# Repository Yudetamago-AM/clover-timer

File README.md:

# clover-timer
Simple Countdown Timer using Padauk MCU

## Docs
- [組み立て方（Japanese）](./docs/assembly-instruction.pdf)
- [補足資料（Japanese）](./docs/assembly-instruction-short.pdf)

## Schematic

Only supports PMS150G for now, but should be able to run on other Padauk MCUs with modifications.

### Power Consumption
- 350 μA (Countdown)
- 55  μA (Sleep)

Fall sleep in 2.5s

## BOM
| Ref | Part # | Description | Purchase | Price |
| --- | ------ | ----------- | -------- | ----- |
| IC1 | Padauk PMS150G | MCU | [LCSC](https://www.lcsc.com/product-detail/Microcontroller-Units-MCUs-MPUs-SOCs_PADAUK-Tech-PMS150G-S08_C2909819.html) | $0.04 each |
| SW1, SW2| TS4548CJ | Push Switch. Others are OK (Check footprint) | [LCSC](https://www.lcsc.com/product-detail/_SHOU-HAN-_C5359333.html) | $0.008 each |
| BZ1 | SFN-1407PA7.6 | Passive Buzzer | [LCSC](https://www.lcsc.com/product-detail/_S-S-_C360603.html) | $0.05 each |
| Battery | CR2032 | 3V Litium Battery Cell | - | $0.1~ each |
| - | Case | 3D printed case | Print by yourself | [STL](./case/bottom_rev0f.stl) |
| - | Binder Clip | Clip for Battery Case | - | $0.05~  each|
| - | Jigu(Optional) | Cardboard Jigu for Battery Case | Cut by yourself | [Data](./case/jigu_laser_rev2.dxf) |
| - | Magnet(Optional) | Φ18*5mm Magnet | - | $0.05~ each |

## Usage

## License
GPLv3

This project is based on:
- [Padauk-tone](https://github.com/Kashouryo/Padauk-tone) by Kashouryo, MIT License
- [pdk-digital-clock](https://github.com/serisman/pdk-digital-clock) by serisman, GPLv3

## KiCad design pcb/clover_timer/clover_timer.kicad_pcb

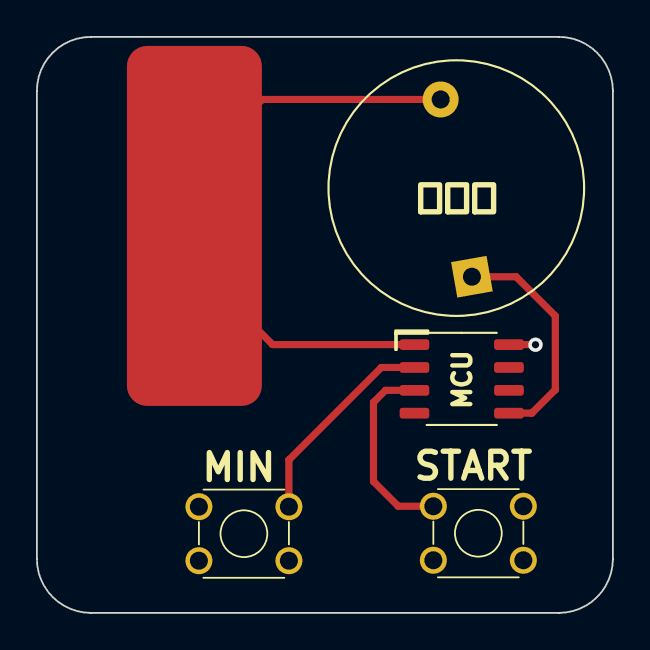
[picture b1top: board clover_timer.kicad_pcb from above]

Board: 2 copper layers, 32.0 x 32.0 mm, 6 parts (1 on the bottom side), 5 nets.

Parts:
BZ1: Buzzer; Buzzer_D14mm_H7mm_P10mm
IC1: PMS150G-S08; SOP-8_3.9x4.9mm_P1.27mm
J1: CR2032_Plus
J2: CR2032_Minus; CR2032_GND
SW1, SW2: SW_Push; SW_TS4548CJ

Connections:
+3V0: BZ1.2 (+), IC1.1 (VDD), J1.1
GND: IC1.8 (GND), J2.1, SW1.1, SW2.1
unnamed: BZ1.1 (-), IC1.5 (PA3)
unnamed: IC1.3 (PA6), SW2.2
unnamed: IC1.2 (PA7), SW1.2

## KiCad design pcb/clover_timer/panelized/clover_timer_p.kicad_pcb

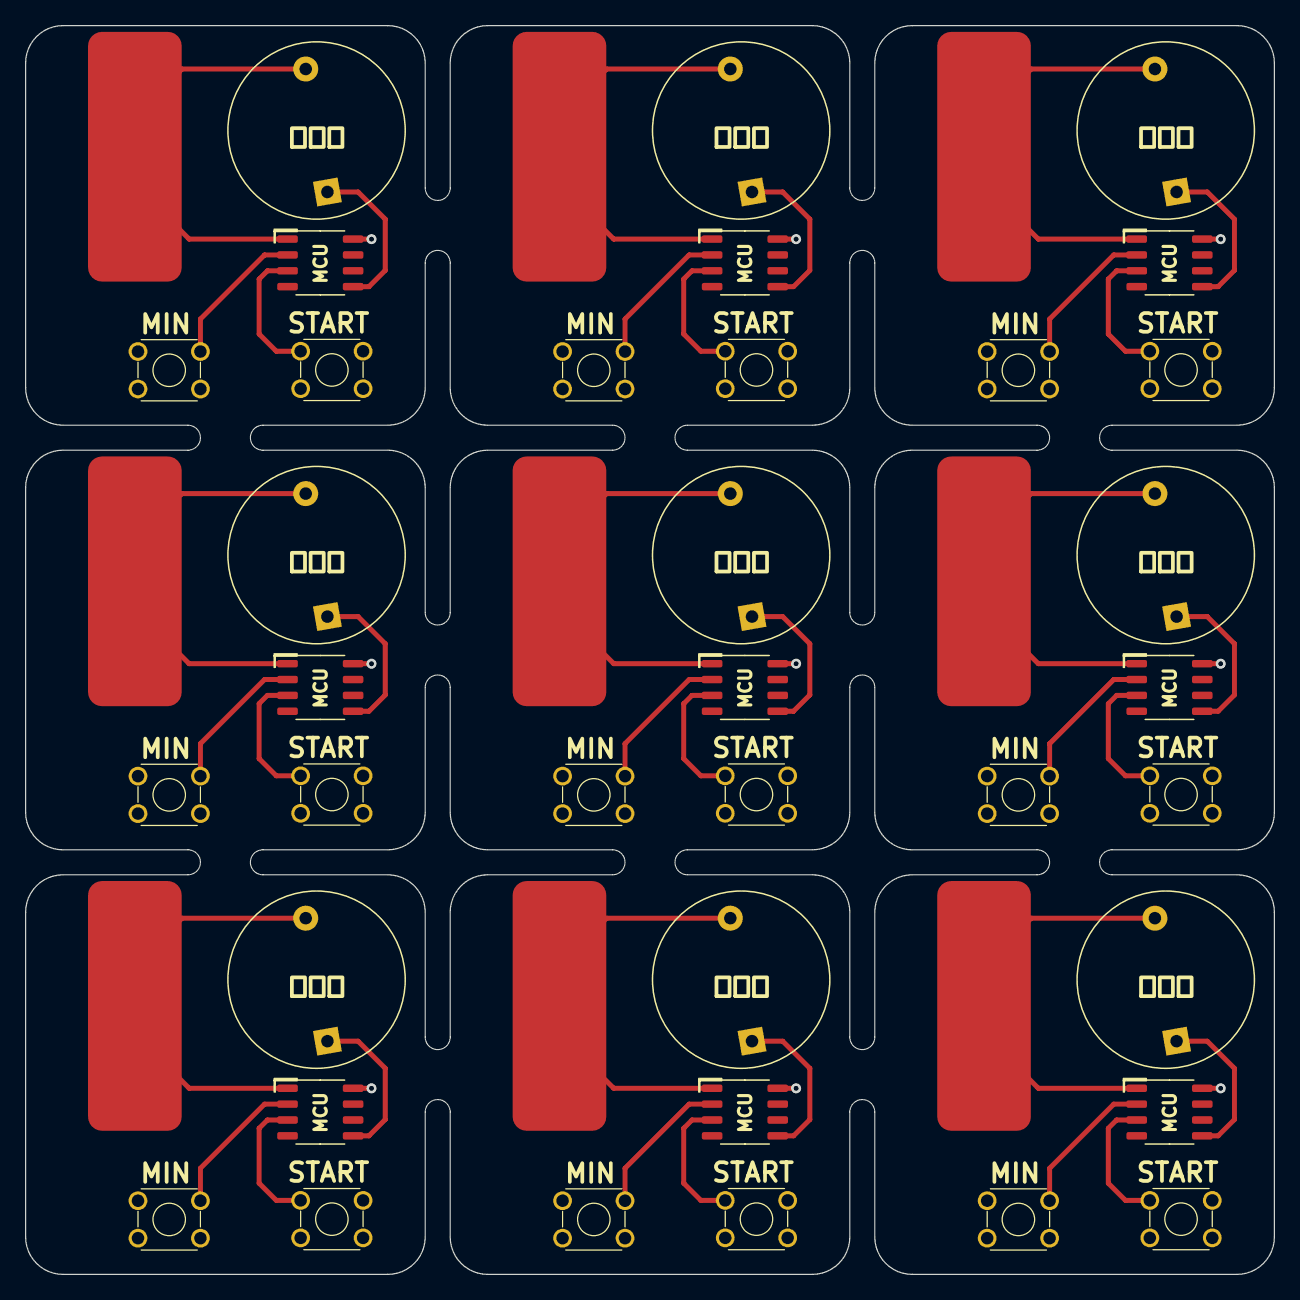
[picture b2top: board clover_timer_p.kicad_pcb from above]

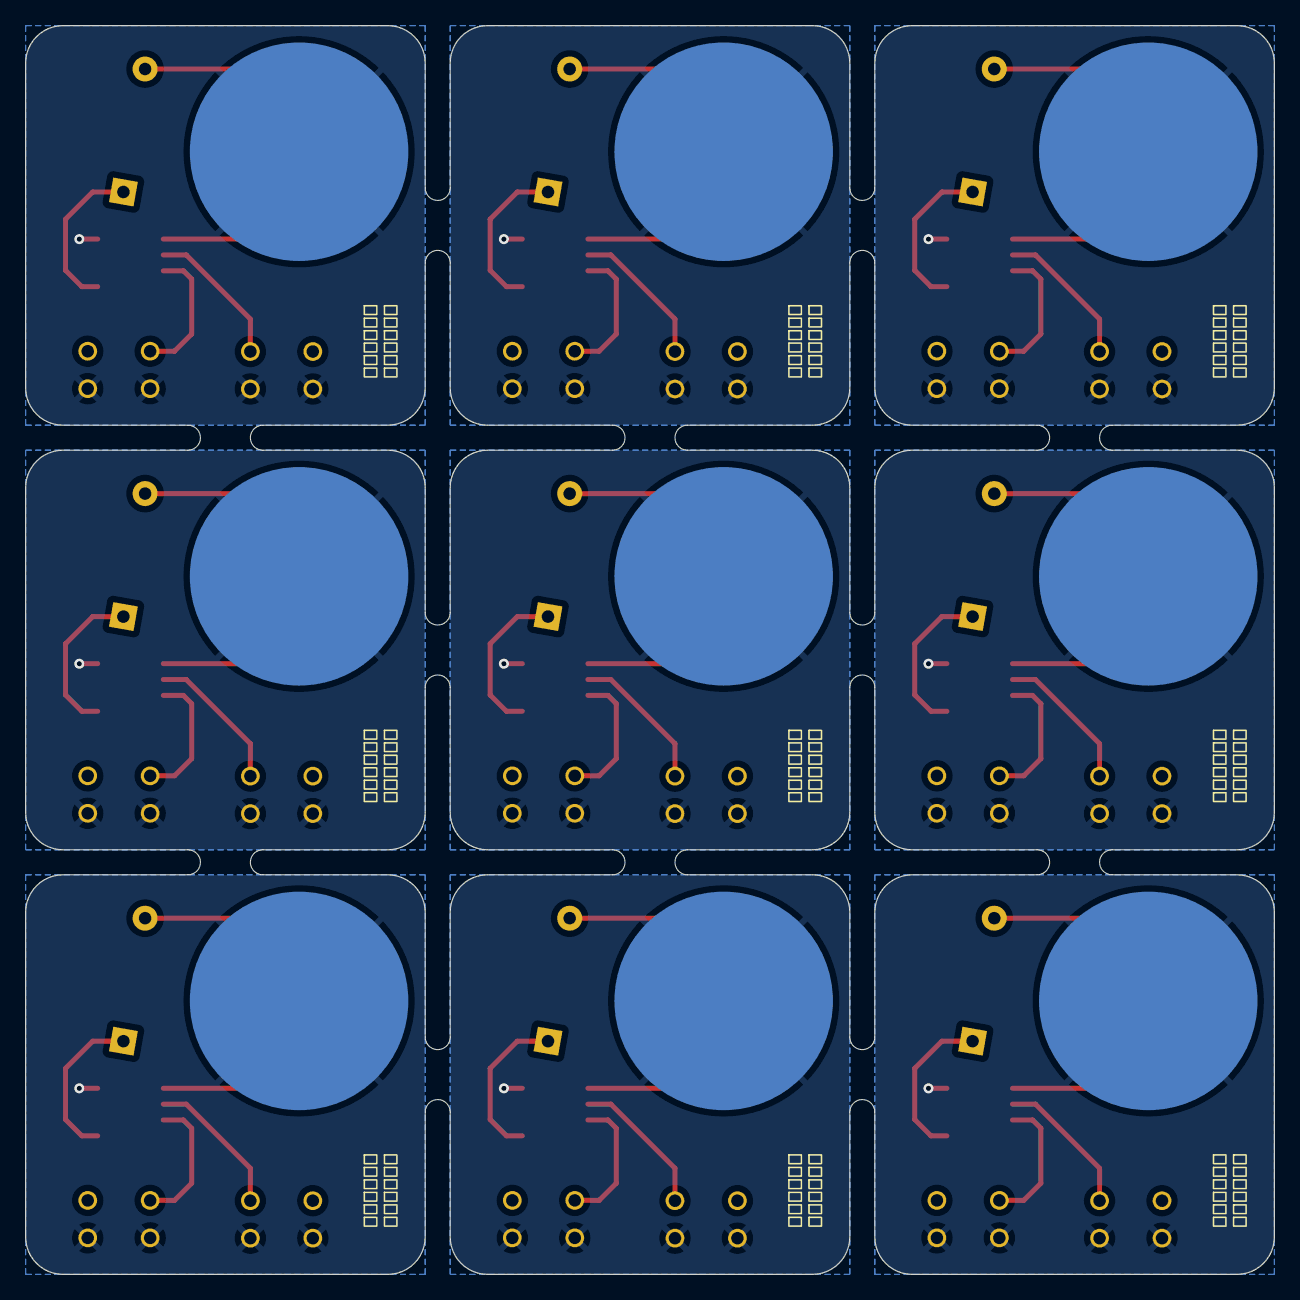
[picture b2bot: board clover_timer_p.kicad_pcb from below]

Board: 2 copper layers, 100.0 x 100.0 mm, 54 parts (9 on the bottom side), 5 nets.

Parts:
BZ1, BZ2, BZ3, BZ4, BZ5, BZ6, BZ7, BZ8, BZ9: Buzzer; Buzzer_D14mm_H7mm_P10mm
IC1, IC2, IC3, IC4, IC5, IC6, IC7, IC8, IC9: PMS150G-S08; SOP-8_3.9x4.9mm_P1.27mm
J1, J3, J5, J7, J9, J11, J13, J15, J17: CR2032_Plus
J2, J4, J6, J8, J10, J12, J14, J16, J18: CR2032_Minus; CR2032_GND
SW1, SW2, SW3, SW4, SW5, SW6, SW7, SW8, SW9, SW10, SW11, SW12, SW13, SW14, SW15, SW16, SW17, SW18: SW_Push; SW_TS4548CJ

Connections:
+3V0: BZ1.2 (+), BZ2.2 (+), BZ3.2 (+), BZ4.2 (+), BZ5.2 (+), BZ6.2 (+), BZ7.2 (+), BZ8.2 (+), BZ9.2 (+), IC1.1 (VDD), IC2.1 (VDD), IC3.1 (VDD), IC4.1 (VDD), IC5.1 (VDD), IC6.1 (VDD), IC7.1 (VDD), IC8.1 (VDD), IC9.1 (VDD), J1.1, J3.1, J5.1, J7.1, J9.1, J11.1, J13.1, J15.1, J17.1
GND: IC1.8 (GND), IC2.8 (GND), IC3.8 (GND), IC4.8 (GND), IC5.8 (GND), IC6.8 (GND), IC7.8 (GND), IC8.8 (GND), IC9.8 (GND), J2.1, J4.1, J6.1, J8.1, J10.1, J12.1, J14.1, J16.1, J18.1, SW1.1, SW2.1, SW3.1, SW4.1, SW5.1, SW6.1, SW7.1, SW8.1, SW9.1, SW10.1, SW11.1, SW12.1, SW13.1, SW14.1, SW15.1, SW16.1, SW17.1, SW18.1
unnamed: BZ1.1 (-), BZ2.1 (-), BZ3.1 (-), BZ4.1 (-), BZ5.1 (-), BZ6.1 (-), BZ7.1 (-), BZ8.1 (-), BZ9.1 (-), IC1.5 (PA3), IC2.5 (PA3), IC3.5 (PA3), IC4.5 (PA3), IC5.5 (PA3), IC6.5 (PA3), IC7.5 (PA3), IC8.5 (PA3), IC9.5 (PA3)
unnamed: IC1.3 (PA6), IC2.3 (PA6), IC3.3 (PA6), IC4.3 (PA6), IC5.3 (PA6), IC6.3 (PA6), IC7.3 (PA6), IC8.3 (PA6), IC9.3 (PA6), SW2.2, SW4.2, SW6.2, SW8.2, SW10.2, SW12.2, SW14.2, SW16.2, SW18.2
unnamed: IC1.2 (PA7), IC2.2 (PA7), IC3.2 (PA7), IC4.2 (PA7), IC5.2 (PA7), IC6.2 (PA7), IC7.2 (PA7), IC8.2 (PA7), IC9.2 (PA7), SW1.2, SW3.2, SW5.2, SW7.2, SW9.2, SW11.2, SW13.2, SW15.2, SW17.2

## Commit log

2023-11-04 add gitignore
2023-11-04 add pcb&firmware
2023-11-04 add case
2023-11-04 Create LICENSE
2023-11-13 update pcb, add docs
2023-11-13 change filenames for shorter URL
2023-11-24 update docs
